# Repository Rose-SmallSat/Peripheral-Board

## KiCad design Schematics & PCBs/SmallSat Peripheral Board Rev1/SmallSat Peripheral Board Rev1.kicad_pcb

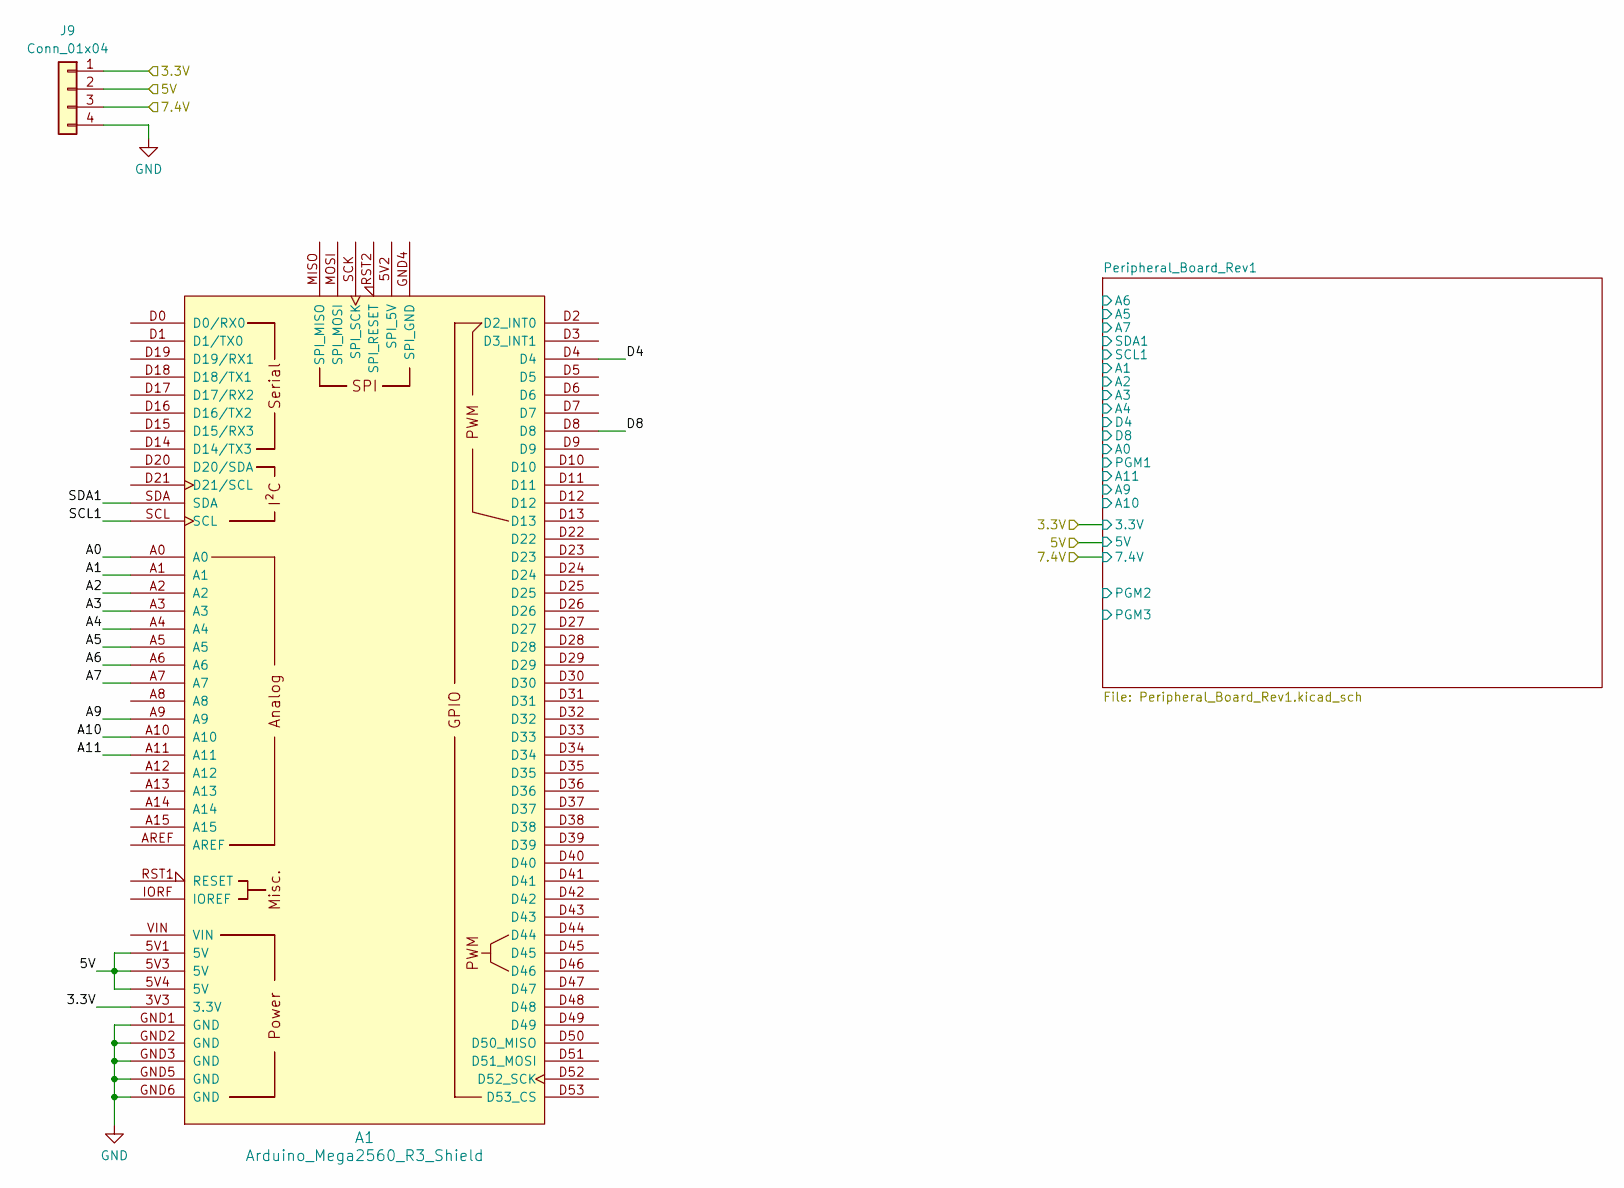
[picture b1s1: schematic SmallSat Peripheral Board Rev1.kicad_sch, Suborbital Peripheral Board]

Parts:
A1: Arduino_Mega2560_R3_Shield
J9: Conn_01x04; PinSocket_1x04_P2.54mm_Vertical

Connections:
/3.3V: J9.1; also elsewhere on the board
/5V: J9.2; also elsewhere on the board
/Peripheral_Board_Rev1/7.4V: J9.3; also elsewhere on the board
GND: A1.GND1 (GND), A1.GND2 (GND), A1.GND3 (GND), A1.GND5 (GND), A1.GND6 (GND), J9.4; also elsewhere on the board
unnamed: A1.5V1 (5V), A1.5V3 (5V), A1.5V4 (5V)

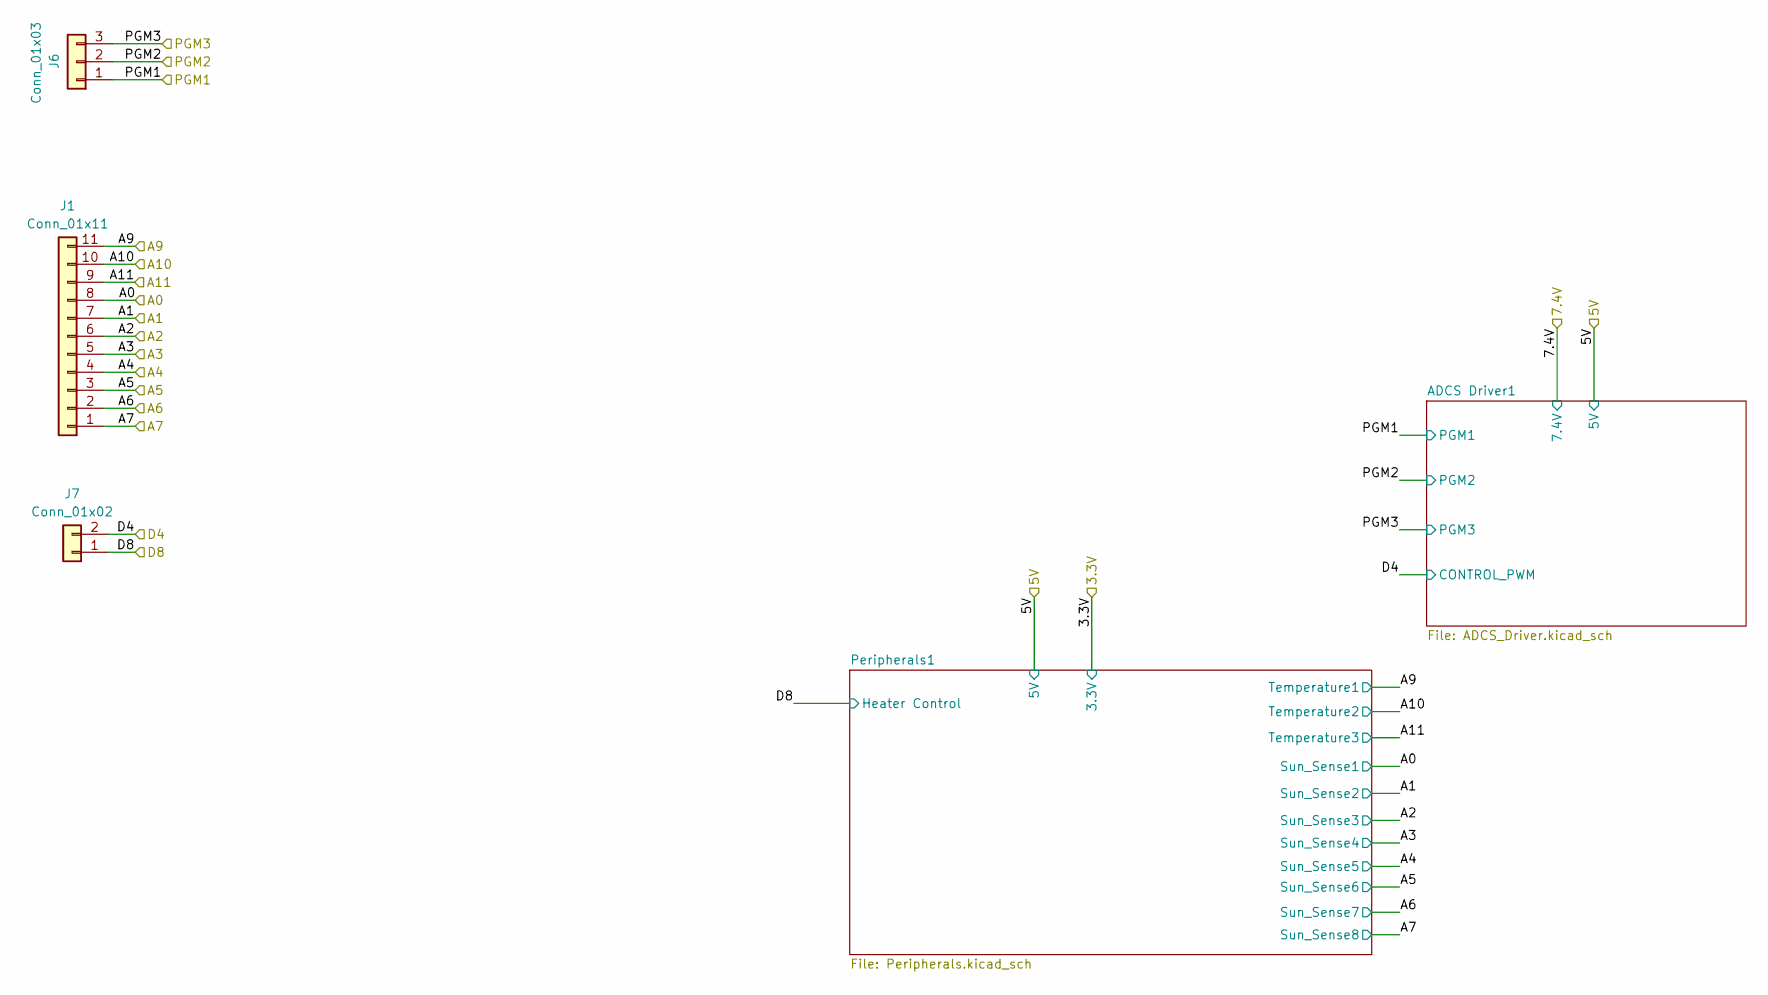
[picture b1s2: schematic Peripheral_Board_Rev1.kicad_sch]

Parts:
J1: Conn_01x11; PinSocket_1x11_P2.54mm_Vertical
J6: Conn_01x03; PinSocket_1x03_P2.54mm_Vertical
J7: Conn_01x02; PinSocket_1x02_P2.54mm_Vertical

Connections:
/Peripheral_Board_Rev1/A0: J1.8; also elsewhere on the board
/Peripheral_Board_Rev1/A1: J1.7; also elsewhere on the board
/Peripheral_Board_Rev1/A2: J1.6; also elsewhere on the board
/Peripheral_Board_Rev1/A3: J1.5; also elsewhere on the board
/Peripheral_Board_Rev1/A4: J1.4; also elsewhere on the board
/Peripheral_Board_Rev1/A5: J1.3; also elsewhere on the board
/Peripheral_Board_Rev1/A6: J1.2; also elsewhere on the board
/Peripheral_Board_Rev1/A7: J1.1; also elsewhere on the board
/Peripheral_Board_Rev1/A9: J1.11; also elsewhere on the board
/Peripheral_Board_Rev1/A10: J1.10; also elsewhere on the board
/Peripheral_Board_Rev1/A11: J1.9; also elsewhere on the board
/Peripheral_Board_Rev1/D4: J7.2; also elsewhere on the board
/Peripheral_Board_Rev1/D8: J7.1; also elsewhere on the board
/Peripheral_Board_Rev1/PGM1: J6.1; also elsewhere on the board
/Peripheral_Board_Rev1/PGM2: J6.2; also elsewhere on the board
/Peripheral_Board_Rev1/PGM3: J6.3; also elsewhere on the board

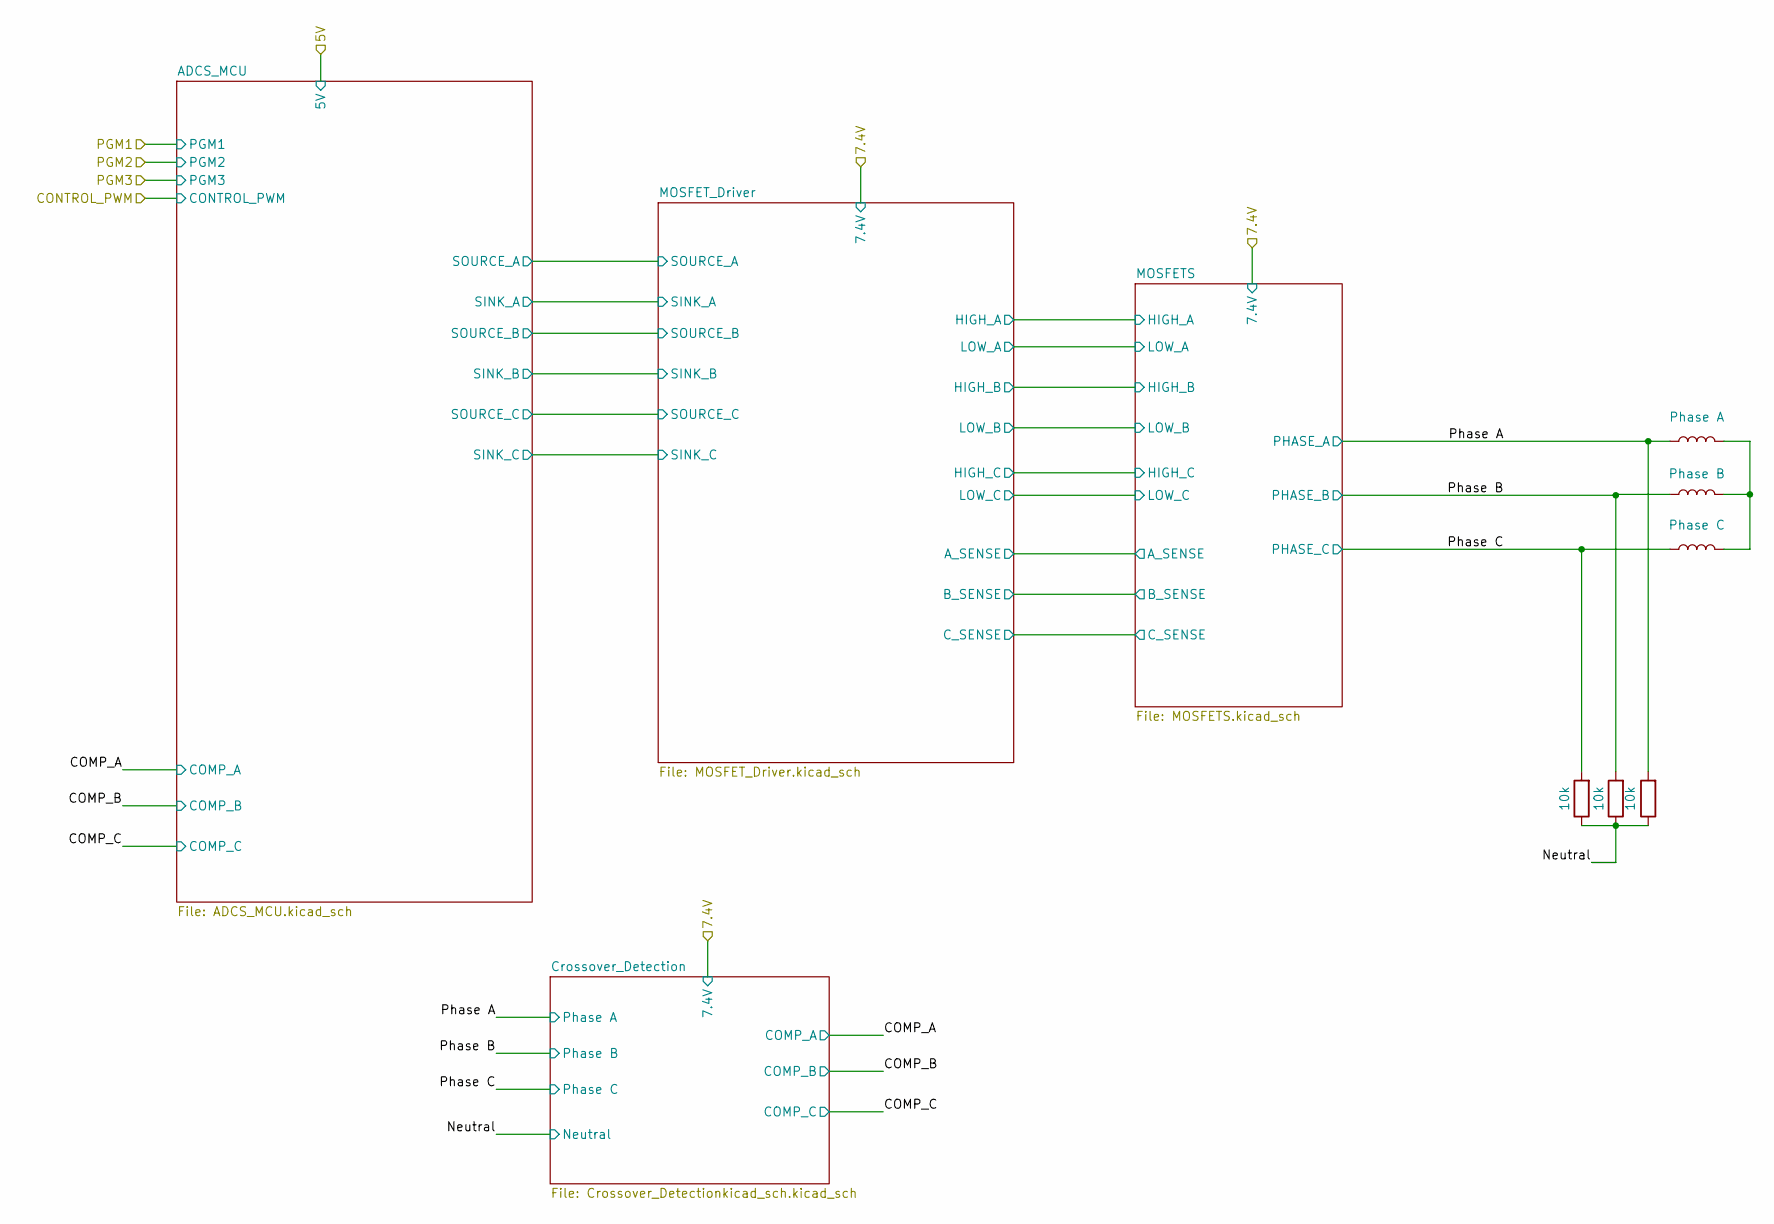
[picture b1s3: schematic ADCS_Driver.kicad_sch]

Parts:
L1: Phase A; PinSocket_1x01_P2.54mm_Vertical
L2: Phase B; PinSocket_1x01_P2.54mm_Vertical
L3: Phase C; PinSocket_1x01_P2.54mm_Vertical
R1, R2, R3: 10k; R_1206_3216Metric

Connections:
/Peripheral_Board_Rev1/ADCS Driver1/Neutral: R1.1, R2.1, R3.1; also elsewhere on the board
/Peripheral_Board_Rev1/ADCS Driver1/Phase A: L1.1, R3.2; also elsewhere on the board
/Peripheral_Board_Rev1/ADCS Driver1/Phase B: L2.1, R2.2; also elsewhere on the board
/Peripheral_Board_Rev1/ADCS Driver1/Phase C: L3.1, R1.2; also elsewhere on the board

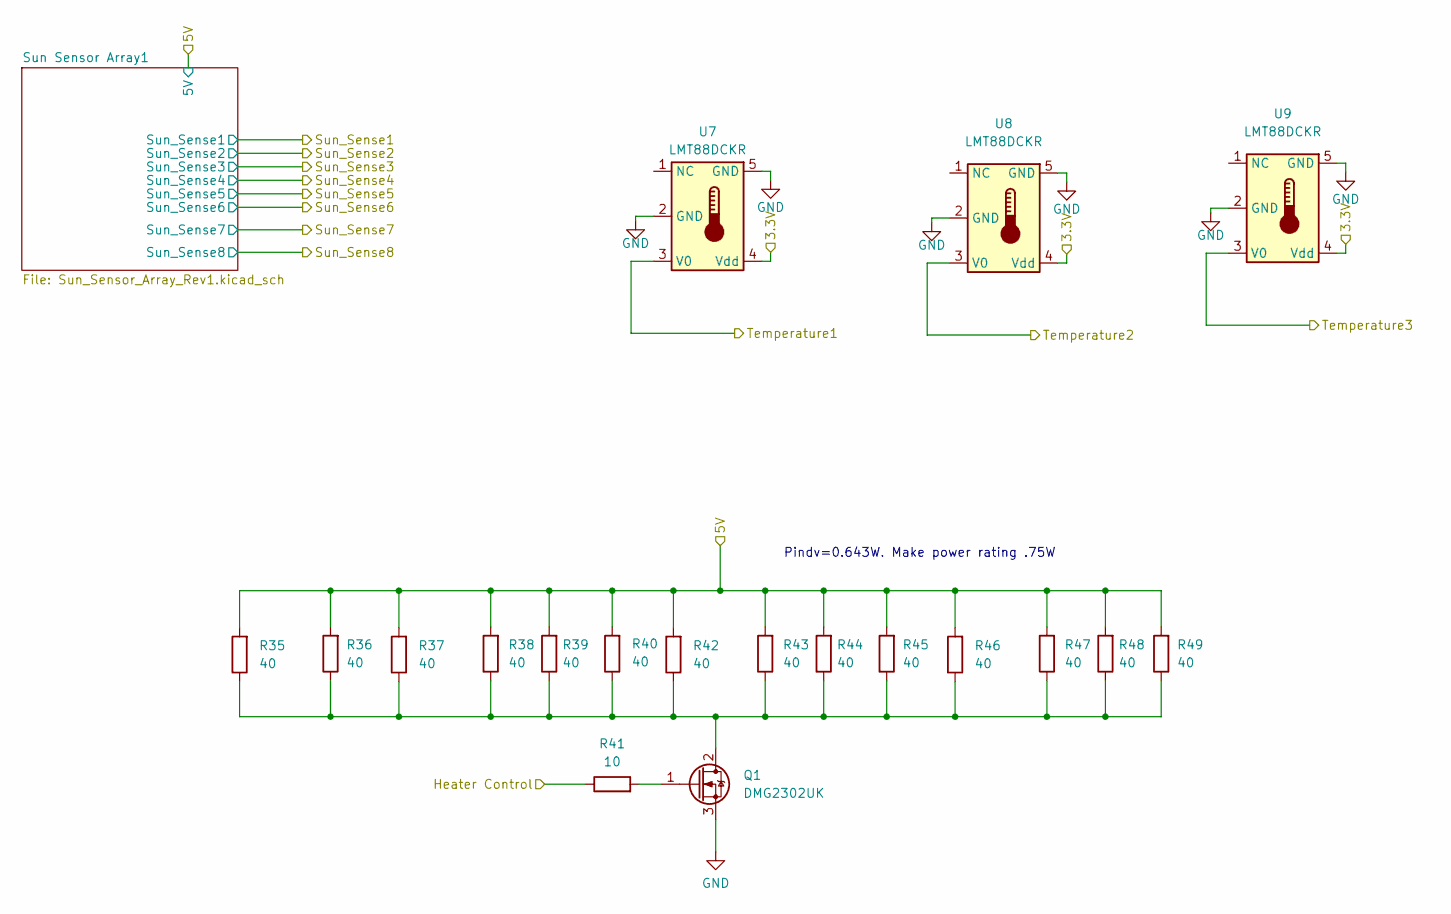
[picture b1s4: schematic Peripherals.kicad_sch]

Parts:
Q1: DMG2302UK; SOT-23
R35, R36, R37, R38, R39, R40, R42, R43, R44, R45, R46, R47, R48, R49: 40; R_1206_3216Metric
R41: 10; R_1206_3216Metric
U7, U8, U9: LMT88DCKR

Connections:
/3.3V: U7.4 (Vdd), U8.4 (Vdd), U9.4 (Vdd); also elsewhere on the board
/5V: R35.2, R36.2, R37.2, R38.2, R39.2, R40.2, R42.2, R43.2, R44.2, R45.2, R46.2, R47.2, R48.2, R49.2; also elsewhere on the board
/Peripheral_Board_Rev1/A9: U7.3 (V0); also elsewhere on the board
/Peripheral_Board_Rev1/A10: U8.3 (V0); also elsewhere on the board
/Peripheral_Board_Rev1/A11: U9.3 (V0); also elsewhere on the board
/Peripheral_Board_Rev1/D8: R41.1; also elsewhere on the board
GND: Q1.3 (S), U7.2 (GND), U7.5 (GND), U8.2 (GND), U8.5 (GND), U9.2 (GND), U9.5 (GND); also elsewhere on the board
unnamed: Q1.2 (D), R35.1, R36.1, R37.1, R38.1, R39.1, R40.1, R42.1, R43.1, R44.1, R45.1, R46.1, R47.1, R48.1, R49.1
unnamed: Q1.1 (G), R41.2

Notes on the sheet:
Pindv=0.643W. Make power rating .75W

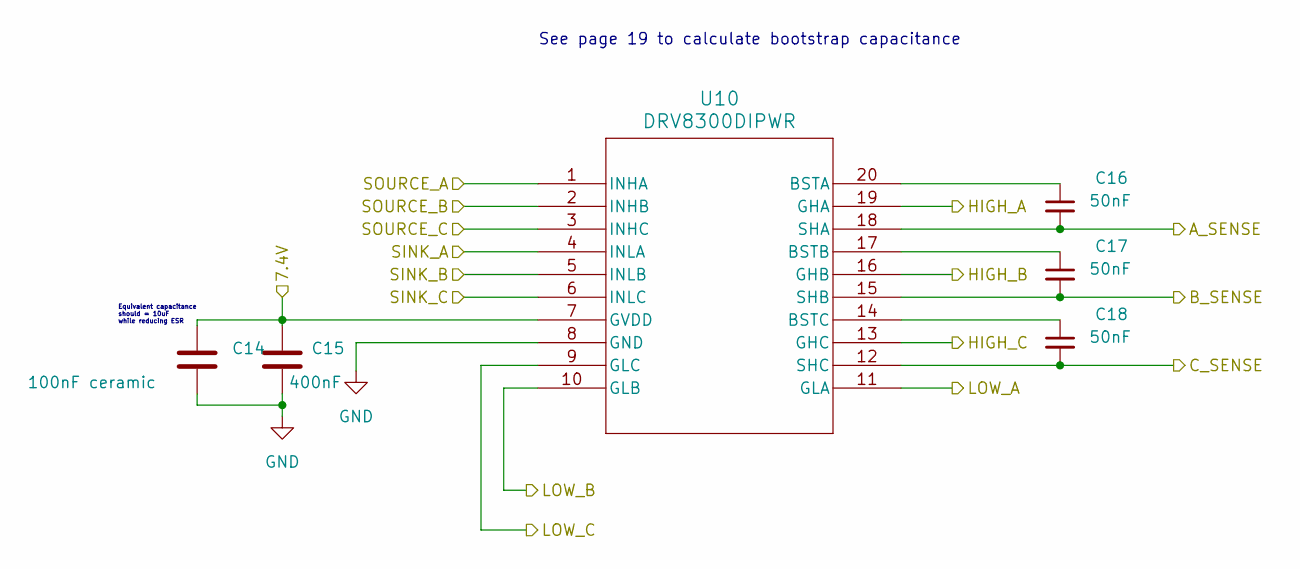
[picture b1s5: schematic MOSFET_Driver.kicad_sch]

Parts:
C14: 100nF ceramic; C_1206_3216Metric
C15: 400nF; C_1206_3216Metric
C16, C17, C18: 50nF; C_1206_3216Metric
U10: DRV8300DIPWR; DRV3800DIPWR

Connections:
/Peripheral_Board_Rev1/7.4V: C14.1, C15.1, U10.7 (GVDD); also elsewhere on the board
/Peripheral_Board_Rev1/ADCS Driver1/ADCS_MCU/SINK_A: U10.4 (INLA); also elsewhere on the board
/Peripheral_Board_Rev1/ADCS Driver1/ADCS_MCU/SINK_B: U10.5 (INLB); also elsewhere on the board
/Peripheral_Board_Rev1/ADCS Driver1/ADCS_MCU/SINK_C: U10.6 (INLC); also elsewhere on the board
/Peripheral_Board_Rev1/ADCS Driver1/ADCS_MCU/SOURCE_A: U10.1 (INHA); also elsewhere on the board
/Peripheral_Board_Rev1/ADCS Driver1/ADCS_MCU/SOURCE_B: U10.2 (INHB); also elsewhere on the board
/Peripheral_Board_Rev1/ADCS Driver1/ADCS_MCU/SOURCE_C: U10.3 (INHC); also elsewhere on the board
/Peripheral_Board_Rev1/ADCS Driver1/MOSFETS/HIGH_A: U10.19 (GHA); also elsewhere on the board
/Peripheral_Board_Rev1/ADCS Driver1/MOSFETS/HIGH_B: U10.16 (GHB); also elsewhere on the board
/Peripheral_Board_Rev1/ADCS Driver1/MOSFETS/HIGH_C: U10.13 (GHC); also elsewhere on the board
/Peripheral_Board_Rev1/ADCS Driver1/MOSFETS/LOW_A: U10.11 (GLA); also elsewhere on the board
/Peripheral_Board_Rev1/ADCS Driver1/MOSFETS/LOW_B: U10.10 (GLB); also elsewhere on the board
/Peripheral_Board_Rev1/ADCS Driver1/MOSFETS/LOW_C: U10.9 (GLC); also elsewhere on the board
/Peripheral_Board_Rev1/ADCS Driver1/Phase A: C16.2, U10.18 (SHA); also elsewhere on the board
/Peripheral_Board_Rev1/ADCS Driver1/Phase B: C17.2, U10.15 (SHB); also elsewhere on the board
/Peripheral_Board_Rev1/ADCS Driver1/Phase C: C18.2, U10.12 (SHC); also elsewhere on the board
GND: C14.2, C15.2, U10.8 (GND); also elsewhere on the board
unnamed: C16.1, U10.20 (BSTA)
unnamed: C17.1, U10.17 (BSTB)
unnamed: C18.1, U10.14 (BSTC)

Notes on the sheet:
See page 19 to calculate bootstrap capacitance
Equivalent capacitance should = 10uF while reducing ESR

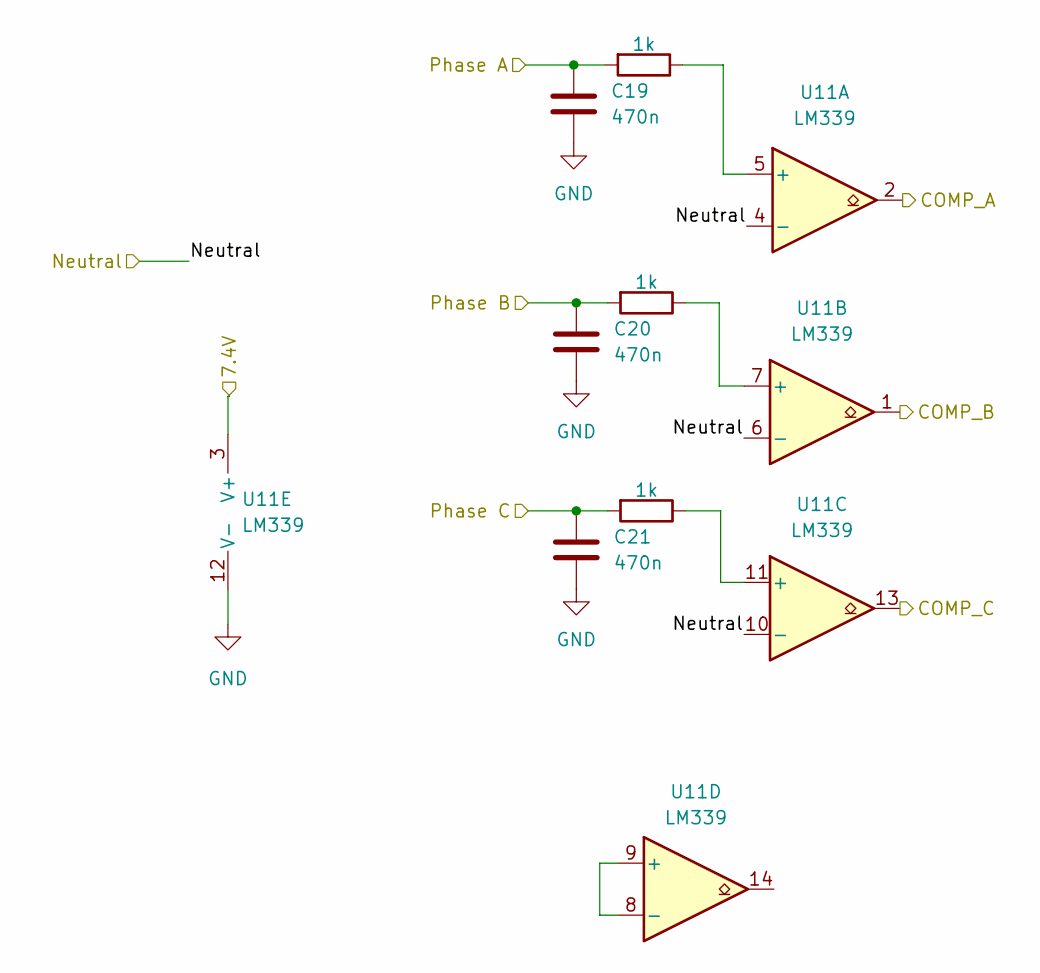
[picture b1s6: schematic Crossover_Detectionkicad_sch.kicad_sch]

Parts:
C19, C20, C21: 470n; C_1206_3216Metric
R56, R57, R58: 1k; R_1206_3216Metric
U11: LM339; LM339_TSSOP14

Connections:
/Peripheral_Board_Rev1/7.4V: U11.3 (V+); also elsewhere on the board
/Peripheral_Board_Rev1/ADCS Driver1/COMP_A: U11.2; also elsewhere on the board
/Peripheral_Board_Rev1/ADCS Driver1/COMP_B: U11.1; also elsewhere on the board
/Peripheral_Board_Rev1/ADCS Driver1/COMP_C: U11.13; also elsewhere on the board
/Peripheral_Board_Rev1/ADCS Driver1/Neutral: U11.4 (-), U11.6 (-), U11.10 (-); also elsewhere on the board
/Peripheral_Board_Rev1/ADCS Driver1/Phase A: C19.1, R56.2; also elsewhere on the board
/Peripheral_Board_Rev1/ADCS Driver1/Phase B: C20.1, R57.2; also elsewhere on the board
/Peripheral_Board_Rev1/ADCS Driver1/Phase C: C21.1, R58.2; also elsewhere on the board
GND: C19.2, C20.2, C21.2, U11.12 (V-); also elsewhere on the board
unnamed: R56.1, U11.5 (+)
unnamed: R57.1, U11.7 (+)
unnamed: R58.1, U11.11 (+)
unnamed: U11.8 (-), U11.9 (+)

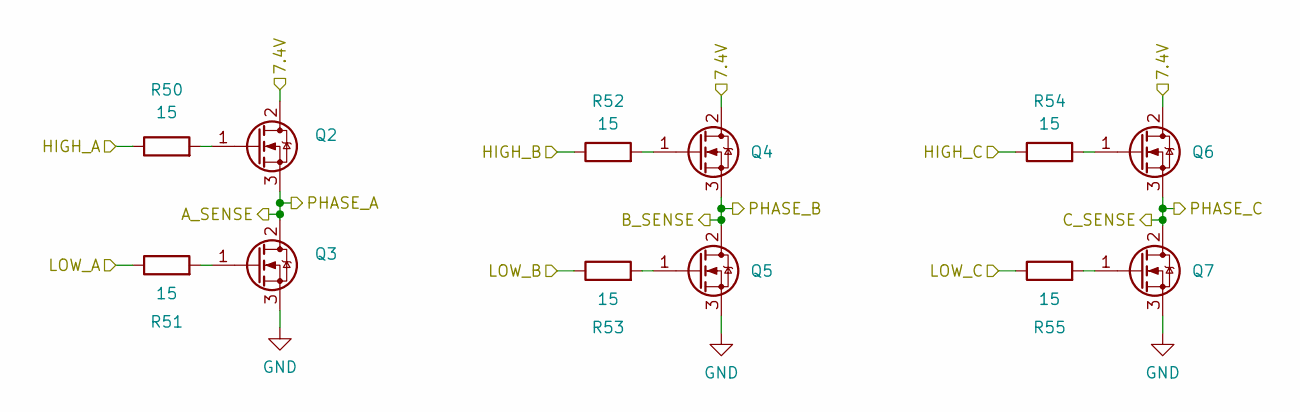
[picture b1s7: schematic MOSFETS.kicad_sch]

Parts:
Q2, Q3, Q4, Q5, Q6, Q7: Q_NMOS_GDS; TO252-3
R50, R51, R52, R53, R54, R55: 15; R_1206_3216Metric

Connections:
/Peripheral_Board_Rev1/7.4V: Q2.2 (D), Q4.2 (D), Q6.2 (D); also elsewhere on the board
/Peripheral_Board_Rev1/ADCS Driver1/MOSFETS/HIGH_A: R50.1; also elsewhere on the board
/Peripheral_Board_Rev1/ADCS Driver1/MOSFETS/HIGH_B: R52.1; also elsewhere on the board
/Peripheral_Board_Rev1/ADCS Driver1/MOSFETS/HIGH_C: R54.1; also elsewhere on the board
/Peripheral_Board_Rev1/ADCS Driver1/MOSFETS/LOW_A: R51.1; also elsewhere on the board
/Peripheral_Board_Rev1/ADCS Driver1/MOSFETS/LOW_B: R53.1; also elsewhere on the board
/Peripheral_Board_Rev1/ADCS Driver1/MOSFETS/LOW_C: R55.1; also elsewhere on the board
/Peripheral_Board_Rev1/ADCS Driver1/Phase A: Q2.3 (S), Q3.2 (D); also elsewhere on the board
/Peripheral_Board_Rev1/ADCS Driver1/Phase B: Q4.3 (S), Q5.2 (D); also elsewhere on the board
/Peripheral_Board_Rev1/ADCS Driver1/Phase C: Q6.3 (S), Q7.2 (D); also elsewhere on the board
GND: Q3.3 (S), Q5.3 (S), Q7.3 (S); also elsewhere on the board
unnamed: Q2.1 (G), R50.2
unnamed: Q3.1 (G), R51.2
unnamed: Q4.1 (G), R52.2
unnamed: Q5.1 (G), R53.2
unnamed: Q6.1 (G), R54.2
unnamed: Q7.1 (G), R55.2

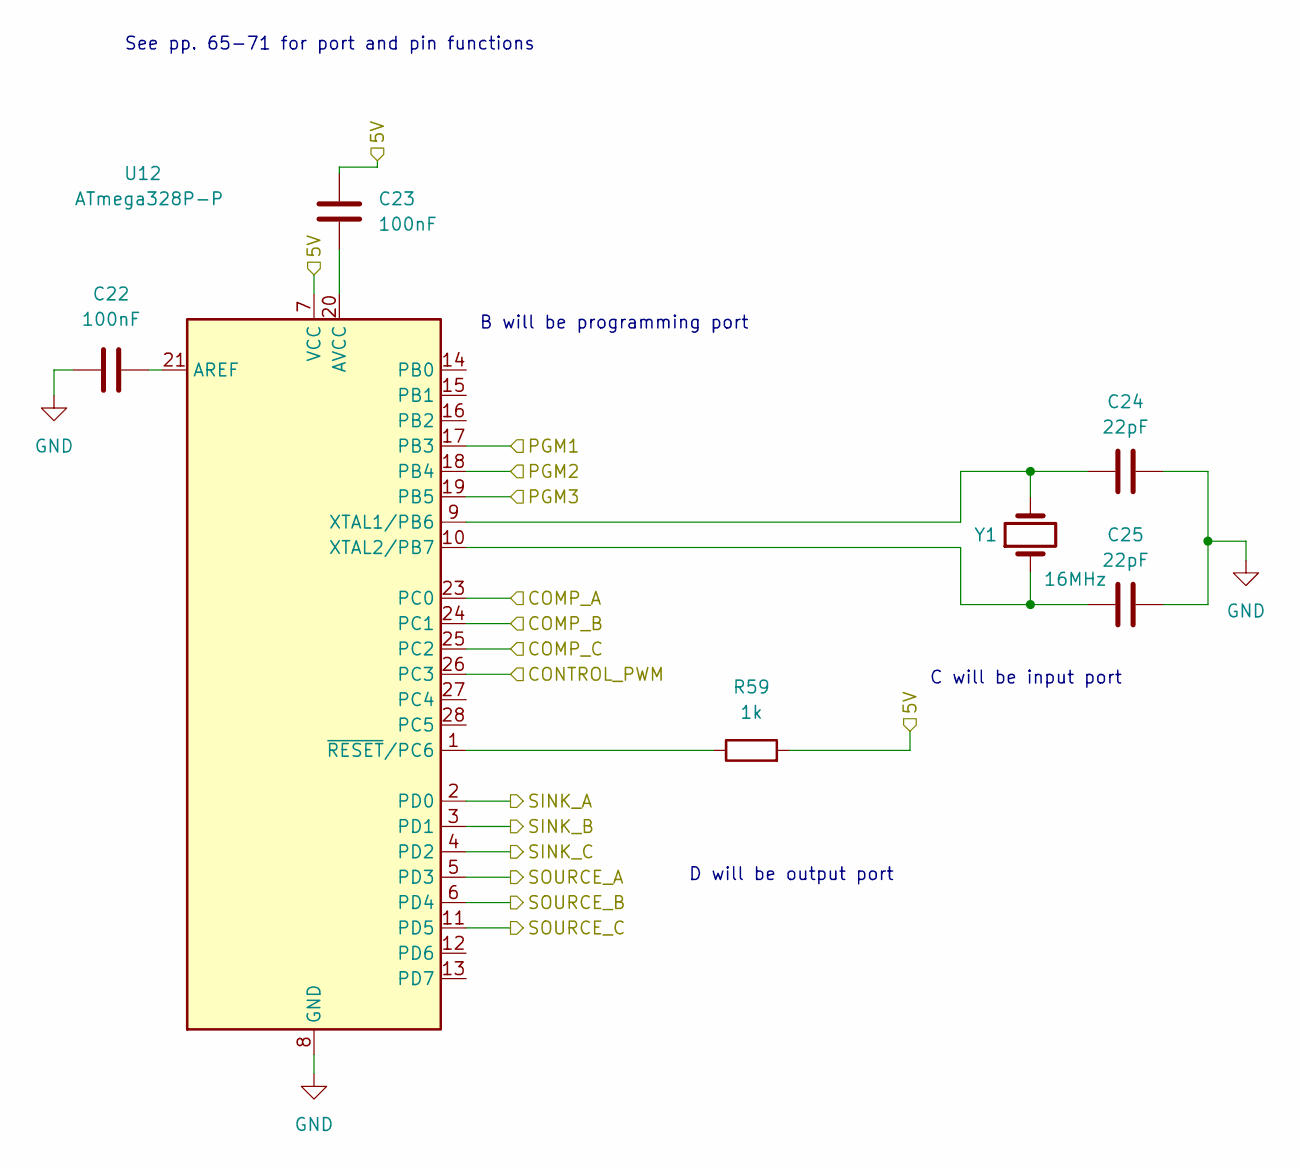
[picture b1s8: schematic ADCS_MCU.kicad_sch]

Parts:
C22, C23: 100nF; C_1206_3216Metric
C24, C25: 22pF; C_1206_3216Metric
R59: 1k; R_1206_3216Metric
U12: ATmega328P-P; DIP-28_W7.62mm
Y1: 16MHz; XTAL_ABLS-4.9152MHZ-K4T

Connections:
/5V: C23.2, R59.2, U12.7 (VCC); also elsewhere on the board
/Peripheral_Board_Rev1/ADCS Driver1/ADCS_MCU/SINK_A: U12.2 (PD0); also elsewhere on the board
/Peripheral_Board_Rev1/ADCS Driver1/ADCS_MCU/SINK_B: U12.3 (PD1); also elsewhere on the board
/Peripheral_Board_Rev1/ADCS Driver1/ADCS_MCU/SINK_C: U12.4 (PD2); also elsewhere on the board
/Peripheral_Board_Rev1/ADCS Driver1/ADCS_MCU/SOURCE_A: U12.5 (PD3); also elsewhere on the board
/Peripheral_Board_Rev1/ADCS Driver1/ADCS_MCU/SOURCE_B: U12.6 (PD4); also elsewhere on the board
/Peripheral_Board_Rev1/ADCS Driver1/ADCS_MCU/SOURCE_C: U12.11 (PD5); also elsewhere on the board
/Peripheral_Board_Rev1/ADCS Driver1/COMP_A: U12.23 (PC0); also elsewhere on the board
/Peripheral_Board_Rev1/ADCS Driver1/COMP_B: U12.24 (PC1); also elsewhere on the board
/Peripheral_Board_Rev1/ADCS Driver1/COMP_C: U12.25 (PC2); also elsewhere on the board
/Peripheral_Board_Rev1/D4: U12.26 (PC3); also elsewhere on the board
/Peripheral_Board_Rev1/PGM1: U12.17 (PB3); also elsewhere on the board
/Peripheral_Board_Rev1/PGM2: U12.18 (PB4); also elsewhere on the board
/Peripheral_Board_Rev1/PGM3: U12.19 (PB5); also elsewhere on the board
GND: C22.1, C24.2, C25.2, U12.8 (GND), U12.22 (GND); also elsewhere on the board
unnamed: C22.2, U12.21 (AREF)
unnamed: C23.1, U12.20 (AVCC)
unnamed: C24.1, U12.9 (XTAL1/PB6), Y1.2
unnamed: C25.1, U12.10 (XTAL2/PB7), Y1.1
unnamed: R59.1, U12.1 (~RESET/PC6)

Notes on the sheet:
D will be output port
See pp. 65-71 for port and pin functions
B will be programming port
C will be input port

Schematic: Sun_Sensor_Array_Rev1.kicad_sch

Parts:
R19, R21, R23, R25, R27, R29, R31, R33: 3k; R_1206_3216Metric
R20, R22, R24, R26, R28, R30, R32, R34: 10k; PinSocket_1x02_P2.54mm_Vertical

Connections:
/5V: R19.1, R21.1, R23.1, R25.1, R27.1, R29.1, R31.1, R33.1; also elsewhere on the board
/Peripheral_Board_Rev1/A0: R33.2, R34.1; also elsewhere on the board
/Peripheral_Board_Rev1/A1: R31.2, R32.1; also elsewhere on the board
/Peripheral_Board_Rev1/A2: R29.2, R30.1; also elsewhere on the board
/Peripheral_Board_Rev1/A3: R27.2, R28.1; also elsewhere on the board
/Peripheral_Board_Rev1/A4: R25.2, R26.1; also elsewhere on the board
/Peripheral_Board_Rev1/A5: R23.2, R24.1; also elsewhere on the board
/Peripheral_Board_Rev1/A6: R21.2, R22.1; also elsewhere on the board
/Peripheral_Board_Rev1/A7: R19.2, R20.1; also elsewhere on the board
GND: R20.2, R22.2, R24.2, R26.2, R28.2, R30.2, R32.2, R34.2; also elsewhere on the board

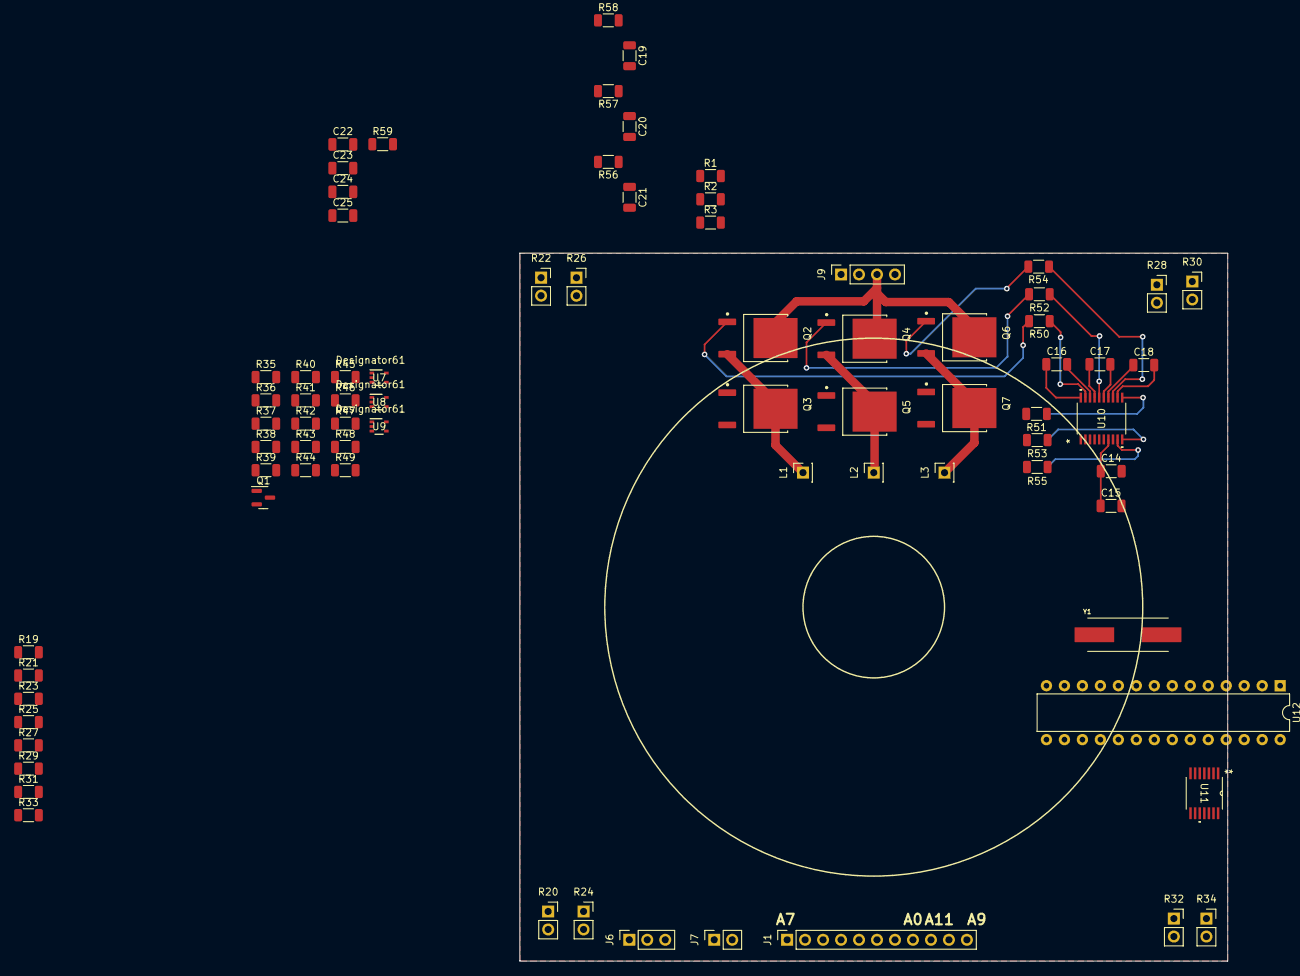
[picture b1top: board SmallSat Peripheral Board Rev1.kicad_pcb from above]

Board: 2 copper layers, 100.0 x 100.0 mm, 77 parts (0 on the bottom side), 59 nets.

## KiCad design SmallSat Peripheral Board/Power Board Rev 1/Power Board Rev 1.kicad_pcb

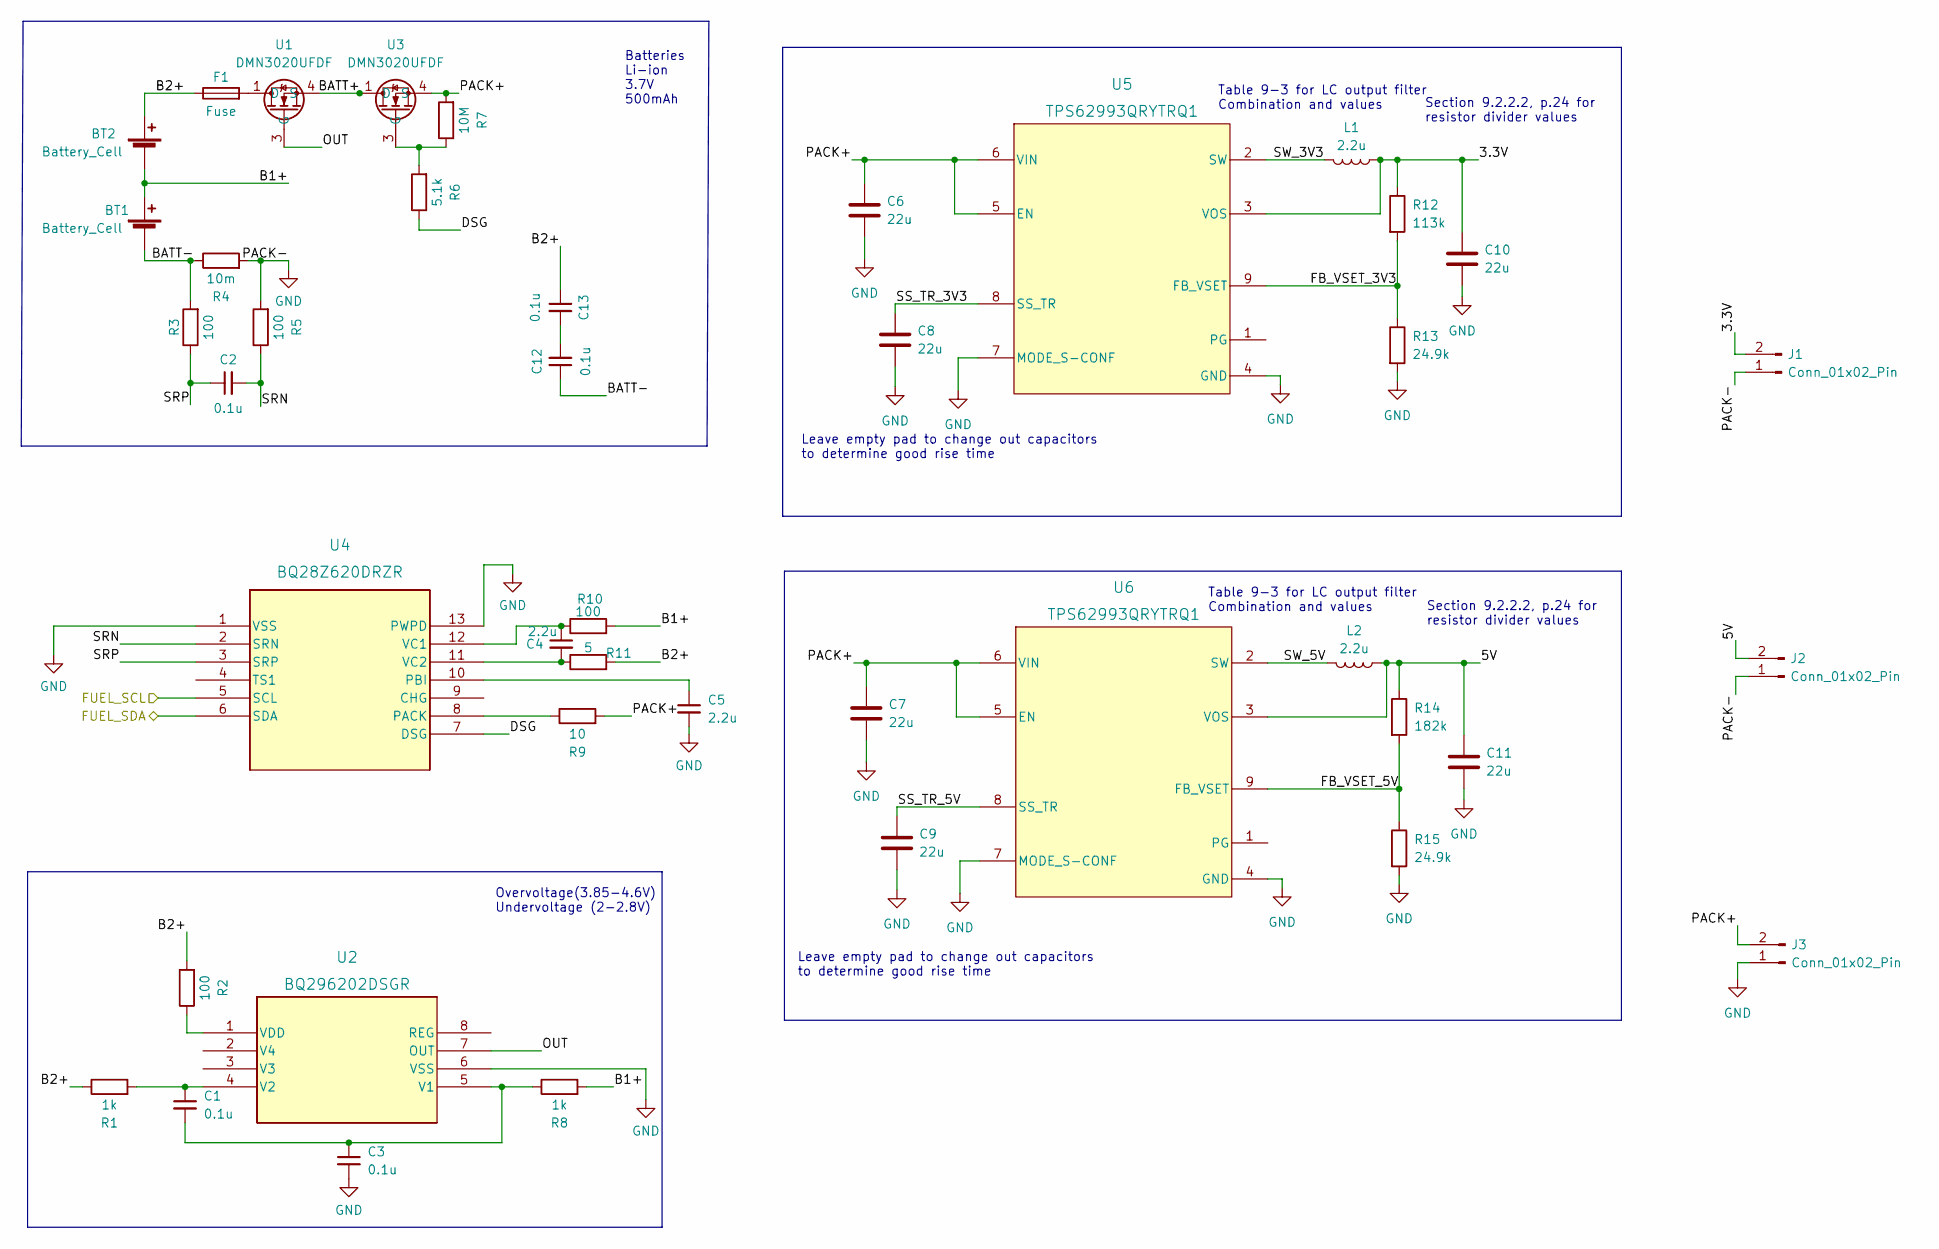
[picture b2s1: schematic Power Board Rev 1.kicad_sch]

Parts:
BT1, BT2: Battery_Cell; BatteryHolder_Keystone_1042_1x18650
C1, C2, C3, C12, C13: 0.1u; C_1206_3216Metric
C4, C5: 2.2u; C_1206_3216Metric
C6, C7, C8, C9, C10, C11: 22u; C_0402_1005Metric
F1: Fuse; Fuse_1206_3216Metric
J1, J2, J3: Conn_01x02_Pin; PinSocket_1x02_P1.00mm_Vertical
L1, L2: 2.2u; L_1206_3216Metric
R1, R8: 1k; R_1206_3216Metric
R2, R3, R5, R10: 100; R_1206_3216Metric
R4: 10m; R_1206_3216Metric
R6: 5.1k; R_1206_3216Metric
R7: 10M; R_1206_3216Metric
R9: 10; R_1206_3216Metric
R11: 5; R_1206_3216Metric
R12: 113k; R_0402_1005Metric
R13, R15: 24.9k; R_0402_1005Metric
R14: 182k; R_0402_1005Metric
U1, U3: DMN3020UFDF; DFN-6-1EP_2x2mm_P0.5mm_EP0.6x1.37mm
U2: BQ296202DSGR; DSG8_TEX
U4: BQ28Z620DRZR; VSON12_DRZ_TEX
U5, U6: TPS62993QRYTRQ1; RYT0009A-MFG

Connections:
/3.3V: C10.1, J1.2, L1.1, R12.1, U5.3 (VOS)
/5V: C11.1, J2.2, L2.1, R14.1, U6.3 (VOS)
/B1+: BT1.1 (+), BT2.2 (-), R8.2, R10.2
/B2+: BT2.1 (+), C13.1, F1.1, R1.1, R2.2, R11.2
/BATT+: U1.4 (S), U3.1 (D)
/BATT-: BT1.2 (-), C12.1, R3.2, R4.1
/DSG: R6.1, U4.7 (DSG)
/Fuel_SCL: U4.5 (SCL); also elsewhere on the board
/Fuel_SDA: U4.6 (SDA); also elsewhere on the board
/OUT: U1.3 (G), U2.7 (OUT)
/PACK+: C6.1, C7.1, J3.2, R7.2, R9.2, U3.4 (S), U5.5 (EN), U5.6 (VIN), U6.5 (EN), U6.6 (VIN)
/SRN: C2.2, R5.1, U4.2 (SRN)
/SRP: C2.1, R3.1, U4.3 (SRP)
/V_Regulation/FB_VSET_3V3: R12.2, R13.1, U5.9 (FB_VSET)
/V_Regulation/FB_VSET_5V: R14.2, R15.1, U6.9 (FB_VSET)
/V_Regulation/SS_TR_3V3: C8.1, U5.8 (SS_TR)
/V_Regulation/SS_TR_5V: C9.1, U6.8 (SS_TR)
/V_Regulation/SW_3V3: L1.2, U5.2 (SW)
/V_Regulation/SW_5V: L2.2, U6.2 (SW)
GND: C3.2, C5.2, C6.2, C7.2, C8.2, C9.2, C10.2, C11.2, J1.1, J2.1, J3.1, R4.2, R5.2, R13.2, R15.2, U2.6 (VSS), U4.1 (VSS), U4.13 (PWPD), U5.4 (GND), U5.7 (MODE_S-CONF), U6.4 (GND), U6.7 (MODE_S-CONF)
unnamed: C12.2, C13.2
unnamed: F1.2, U1.1 (D)
unnamed: C1.2, C3.1, R8.1, U2.5 (V1)
unnamed: C1.1, R1.2, U2.4 (V2)
unnamed: R2.1, U2.1 (VDD)
unnamed: R6.2, R7.1, U3.3 (G)
unnamed: R9.1, U4.8 (PACK)
unnamed: C5.1, U4.10 (PBI)
unnamed: C4.1, R10.1, U4.12 (VC1)
unnamed: C4.2, R11.1, U4.11 (VC2)

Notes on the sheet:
Batteries Li-ion 3.7V 500mAh
Table 9-3 for LC output filter Combination and values
Overvoltage(3.85-4.6V) Undervoltage (2-2.8V)
Section 9.2.2.2, p.24 for resistor divider values
Leave empty pad to change out capacitors to determine good rise time
